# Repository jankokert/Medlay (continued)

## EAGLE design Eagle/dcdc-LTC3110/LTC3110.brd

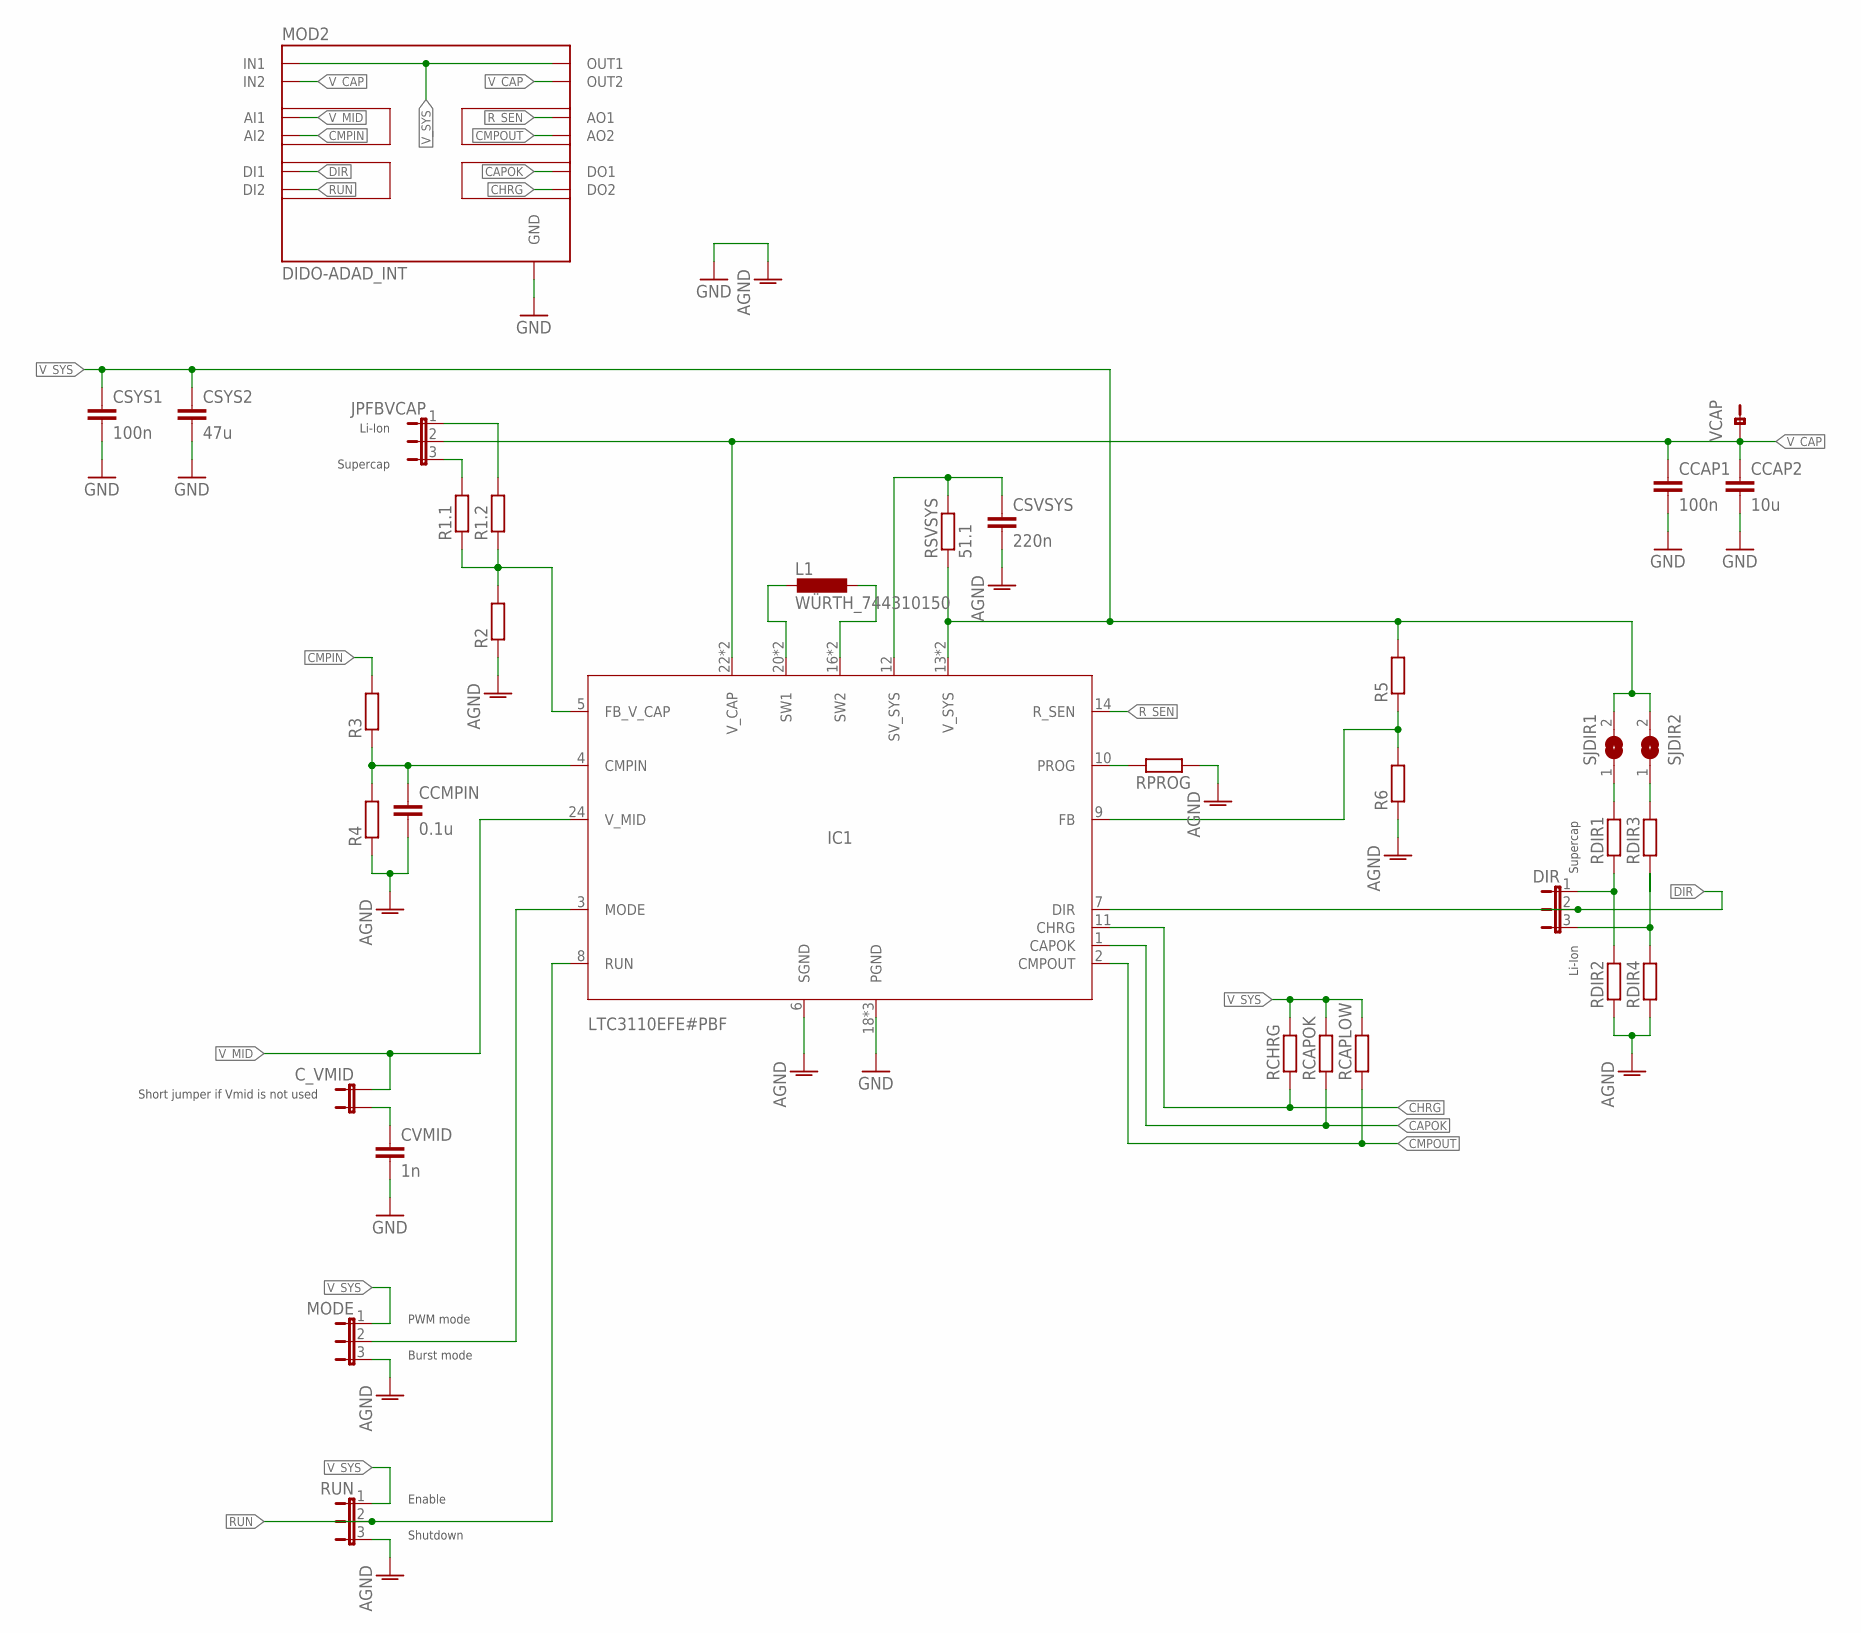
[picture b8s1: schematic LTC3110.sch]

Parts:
CCAP1: 100n; C0805
CCAP2: 10u; C0805
CCMPIN: 0.1u; C0805
CSVSYS: 220n; C0805
CSYS1: 100n; C0805
CSYS2: 47u; C0805
CVMID: 1n; C0805
C_VMID: JP2_SMALL_PAD
DIR: JP3_SMALL_PAD
IC1: LTC3110EFE#PBF; TSSOP24-4,4MM
JPFBVCAP: JP3_SMALL_PAD
L1: WÜRTH_744310150
MOD2: DIDO-ADAD_INT; DIDO-ADAD
MODE: JP3_SMALL_PAD
R1.1, R1.2, R2, R3, R4, R5, R6: R-EU_R0805; R0805
RCAPLOW: R-EU_R0805; R0805
RCAPOK: R-EU_R0805; R0805
RCHRG: R-EU_R0805; R0805
RDIR1, RDIR2, RDIR3, RDIR4: R-EU_R0805; R0805
RPROG: R-EU_R0805; R0805
RSVSYS: 51.1; R0805
RUN: JP3_SMALL_PAD
SJDIR1, SJDIR2: SJ2
VCAP: JPO; JP0

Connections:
AGND: CCMPIN.2, CSVSYS.2, IC1.6 (SGND), MODE.3, R2.1, R4.1, R6.1, RDIR2.1, RDIR4.1, RPROG.1, RUN.3
CAPOK: IC1.1 (CAPOK), MOD2.DO1, RCAPOK.1
CHRG: IC1.11 (CHRG), MOD2.DO2, RCHRG.1
CMPIN: MOD2.AI2, R3.2
CMPOUT: IC1.2 (CMPOUT), MOD2.AO2, RCAPLOW.1
DIR: DIR.2, IC1.7 (DIR), MOD2.DI1
FB_V_CAP: IC1.5 (FB_V_CAP), R1.1.1, R1.2.1, R2.2
GND: CCAP1.2, CCAP2.2, CSYS1.2, CSYS2.2, CVMID.2, IC1.18 (PGND), IC1.19 (PGND), IC1.TAB (PGND), MOD2.GND1 (GND), MOD2.GND2 (GND), MOD2.GND3 (GND), MOD2.GND4 (GND)
MODE: IC1.3 (MODE), MODE.2
unnamed: CVMID.1, C_VMID.2
unnamed: IC1.9 (FB), R5.1, R6.2
unnamed: CCMPIN.1, IC1.4 (CMPIN), R3.1, R4.2
unnamed: CSVSYS.1, IC1.12 (SV_SYS), RSVSYS.2
unnamed: DIR.3, RDIR3.1, RDIR4.2
unnamed: IC1.20 (SW1), IC1.21 (SW1), L1.P$1 (1)
unnamed: IC1.16 (SW2), IC1.17 (SW2), L1.P$2 (2)
unnamed: IC1.10 (PROG), RPROG.2
unnamed: JPFBVCAP.3, R1.1.2
unnamed: DIR.1, RDIR1.1, RDIR2.2
unnamed: JPFBVCAP.1, R1.2.2
unnamed: RDIR1.2, SJDIR1.1
unnamed: RDIR3.2, SJDIR2.1
RUN: IC1.8 (RUN), MOD2.DI2, RUN.2
R_SEN: IC1.14 (R_SEN), MOD2.AO1
V_CAP: CCAP1.1, CCAP2.1, IC1.22 (V_CAP), IC1.23 (V_CAP), JPFBVCAP.2, MOD2.IN2_1 (IN2), MOD2.IN2_2 (IN2), MOD2.IN2_3 (IN2), MOD2.IN2_4 (IN2), MOD2.OUT2_1 (OUT2), MOD2.OUT2_2 (OUT2), MOD2.OUT2_3 (OUT2), MOD2.OUT2_4 (OUT2), VCAP.1
V_MID: C_VMID.1, IC1.24 (V_MID), MOD2.AI1
V_SYS: CSYS1.1, CSYS2.1, IC1.13 (V_SYS), IC1.15 (V_SYS), MOD2.IN1_1 (IN1), MOD2.IN1_2 (IN1), MOD2.IN1_3 (IN1), MOD2.IN1_4 (IN1), MOD2.OUT1_1 (OUT1), MOD2.OUT1_2 (OUT1), MOD2.OUT1_3 (OUT1), MOD2.OUT1_4 (OUT1), MODE.1, R5.2, RCAPLOW.2, RCAPOK.2, RCHRG.2, RSVSYS.1, RUN.1, SJDIR1.2, SJDIR2.2

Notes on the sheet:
Li-Ion
Supercap
PWM mode
Burst mode
Enable
Shutdown
Short jumper if Vmid is not used

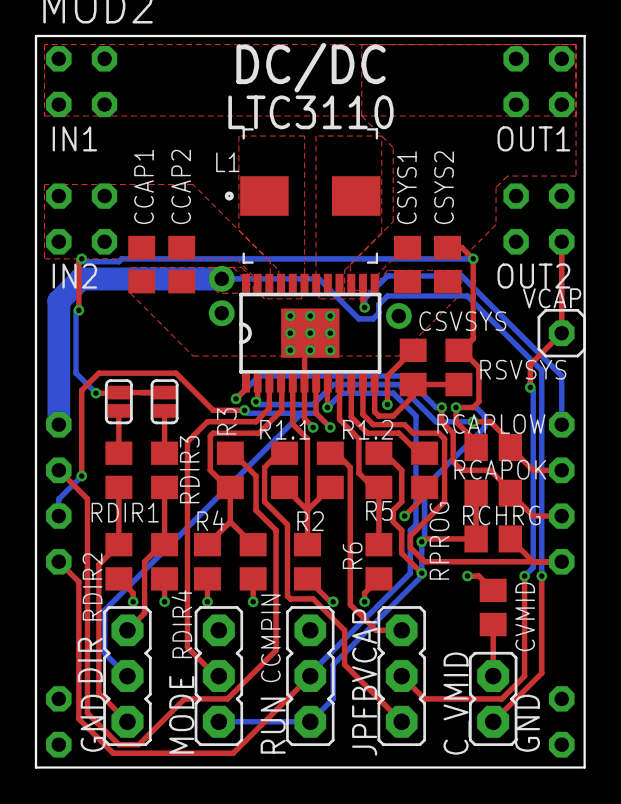
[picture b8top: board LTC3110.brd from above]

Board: 2 copper layers, 30.5 x 40.6 mm, 34 parts (0 on the bottom side), 27 nets.
